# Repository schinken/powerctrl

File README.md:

# DEPRECATED!

For a modern version, look here: https://github.com/b4ckspace/PowerControl

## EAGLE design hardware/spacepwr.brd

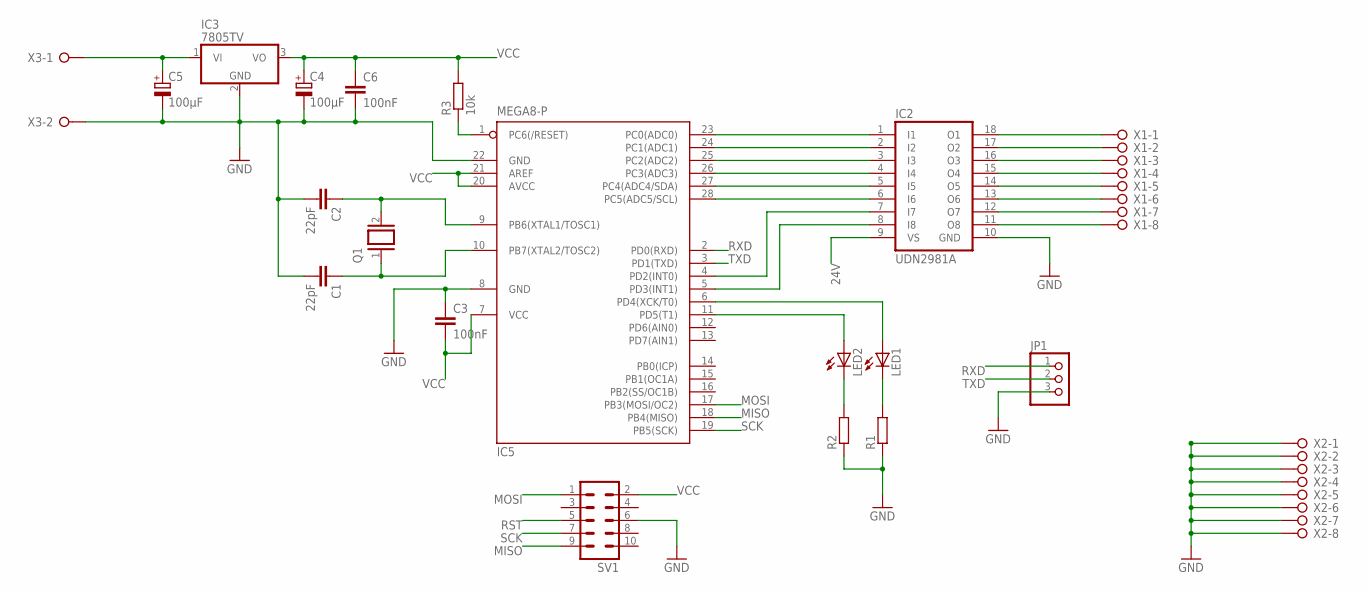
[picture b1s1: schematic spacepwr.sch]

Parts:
C1, C2: 22pF; C025-030X050
C3, C6: 100nF; C025-030X050
C4, C5: 100µF; E5-10,5
IC2: UDN2981A; DIL18
IC3: 7805TV; TO220V
IC5: MEGA8-P; DIL28-3
JP1: PINHD-1X3; 1X03
LED1, LED2: LED5MM
Q1: XTAL/S; QS
R1, R2: R-EU_0207/10; 0207/10
R3: 10k; 0207/10
SV1: ML10
X1, X2: W237-08P; W237-8P
X3: W237-02P; W237-132

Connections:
24V: C5.+, IC2.9 (VS), IC3.1 (VI), X3.1
GND: C1.2, C2.2, C3.1, C4.-, C5.-, C6.2, IC2.10 (GND), IC3.2 (GND), IC5.8 (GND), IC5.22 (GND), JP1.3, R1.1, R2.1, SV1.6, X2.1, X2.2, X2.3, X2.4, X2.5, X2.6, X2.7, X2.8, X3.2
MISO: IC5.18 (PB4(MISO)), SV1.9
MOSI: IC5.17 (PB3(MOSI/OC2)), SV1.1
unnamed: IC2.1 (I1), IC5.23 (PC0(ADC0))
unnamed: IC2.2 (I2), IC5.24 (PC1(ADC1))
unnamed: IC2.3 (I3), IC5.25 (PC2(ADC2))
unnamed: IC2.4 (I4), IC5.26 (PC3(ADC3))
unnamed: IC2.5 (I5), IC5.27 (PC4(ADC4/SDA))
unnamed: IC2.6 (I6), IC5.28 (PC5(ADC5/SCL))
unnamed: IC2.7 (I7), IC5.4 (PD2(INT0))
unnamed: IC2.8 (I8), IC5.5 (PD3(INT1))
unnamed: LED1.K (C), R1.2
unnamed: IC5.6 (PD4(XCK/T0)), LED1.A
unnamed: IC2.18 (O1), X1.1
unnamed: IC5.11 (PD5(T1)), LED2.A
unnamed: LED2.K (C), R2.2
unnamed: IC2.17 (O2), X1.2
unnamed: IC2.16 (O3), X1.3
unnamed: IC2.15 (O4), X1.4
unnamed: C1.1, IC5.10 (PB7(XTAL2/TOSC2)), Q1.1
unnamed: C2.1, IC5.9 (PB6(XTAL1/TOSC1)), Q1.2
unnamed: IC2.14 (O5), X1.5
unnamed: IC2.13 (O6), X1.6
unnamed: IC2.12 (O7), X1.7
unnamed: IC2.11 (O8), X1.8
RST: IC5.1 (PC6(/RESET)), R3.1, SV1.5
RXD: IC5.2 (PD0(RXD)), JP1.1
SCK: IC5.19 (PB5(SCK)), SV1.7
TXD: IC5.3 (PD1(TXD)), JP1.2
VCC: C3.2, C4.+, C6.1, IC3.3 (VO), IC5.7 (VCC), IC5.20 (AVCC), IC5.21 (AREF), R3.2, SV1.2

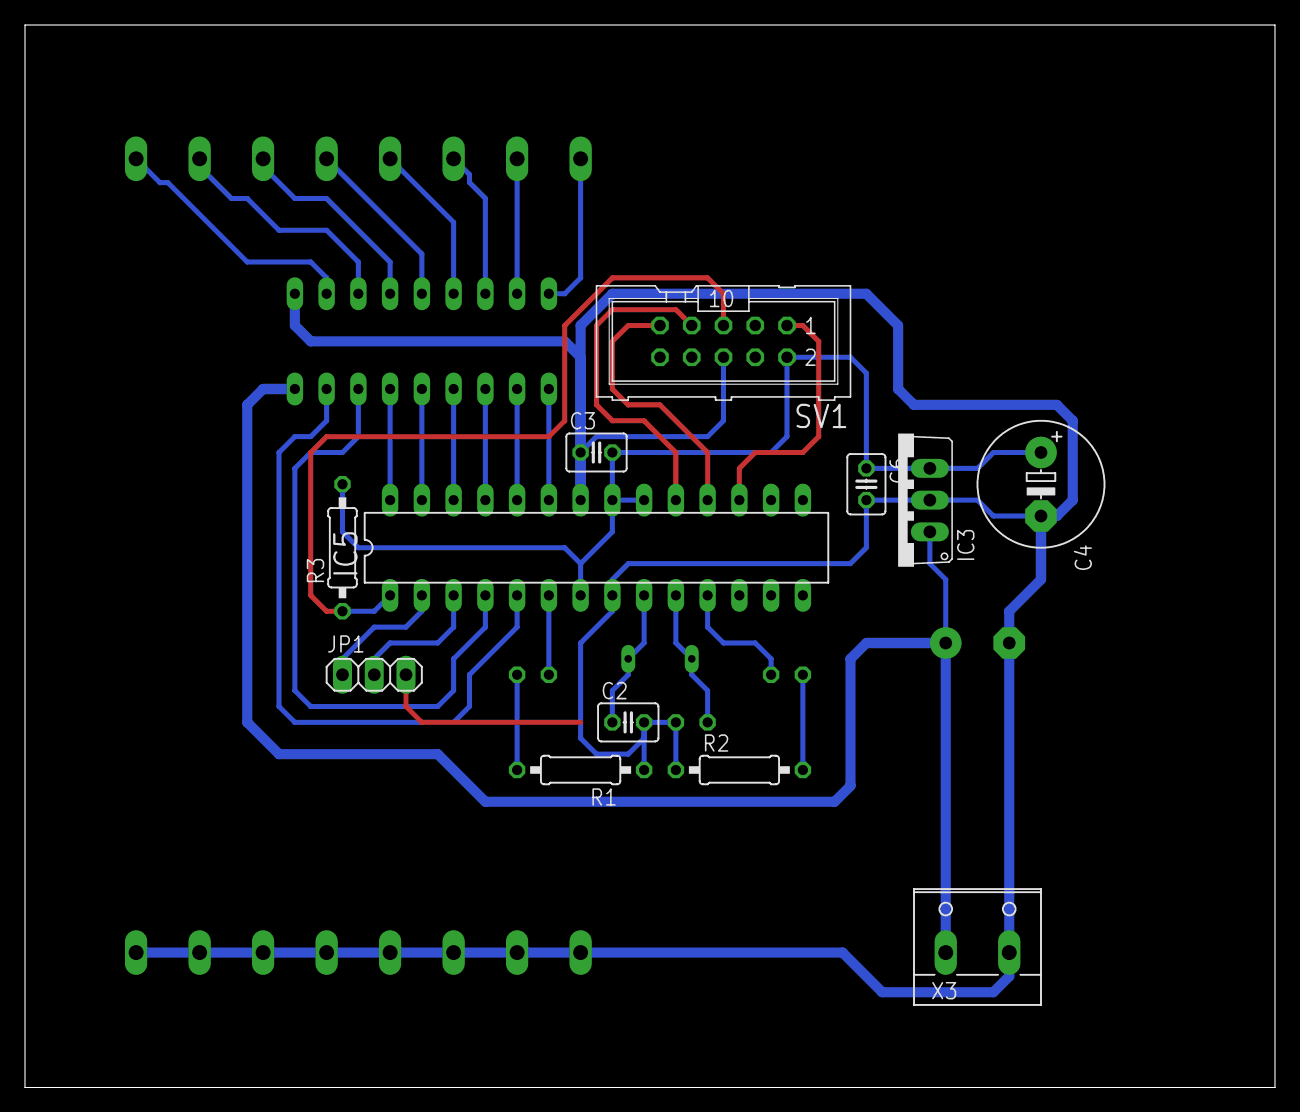
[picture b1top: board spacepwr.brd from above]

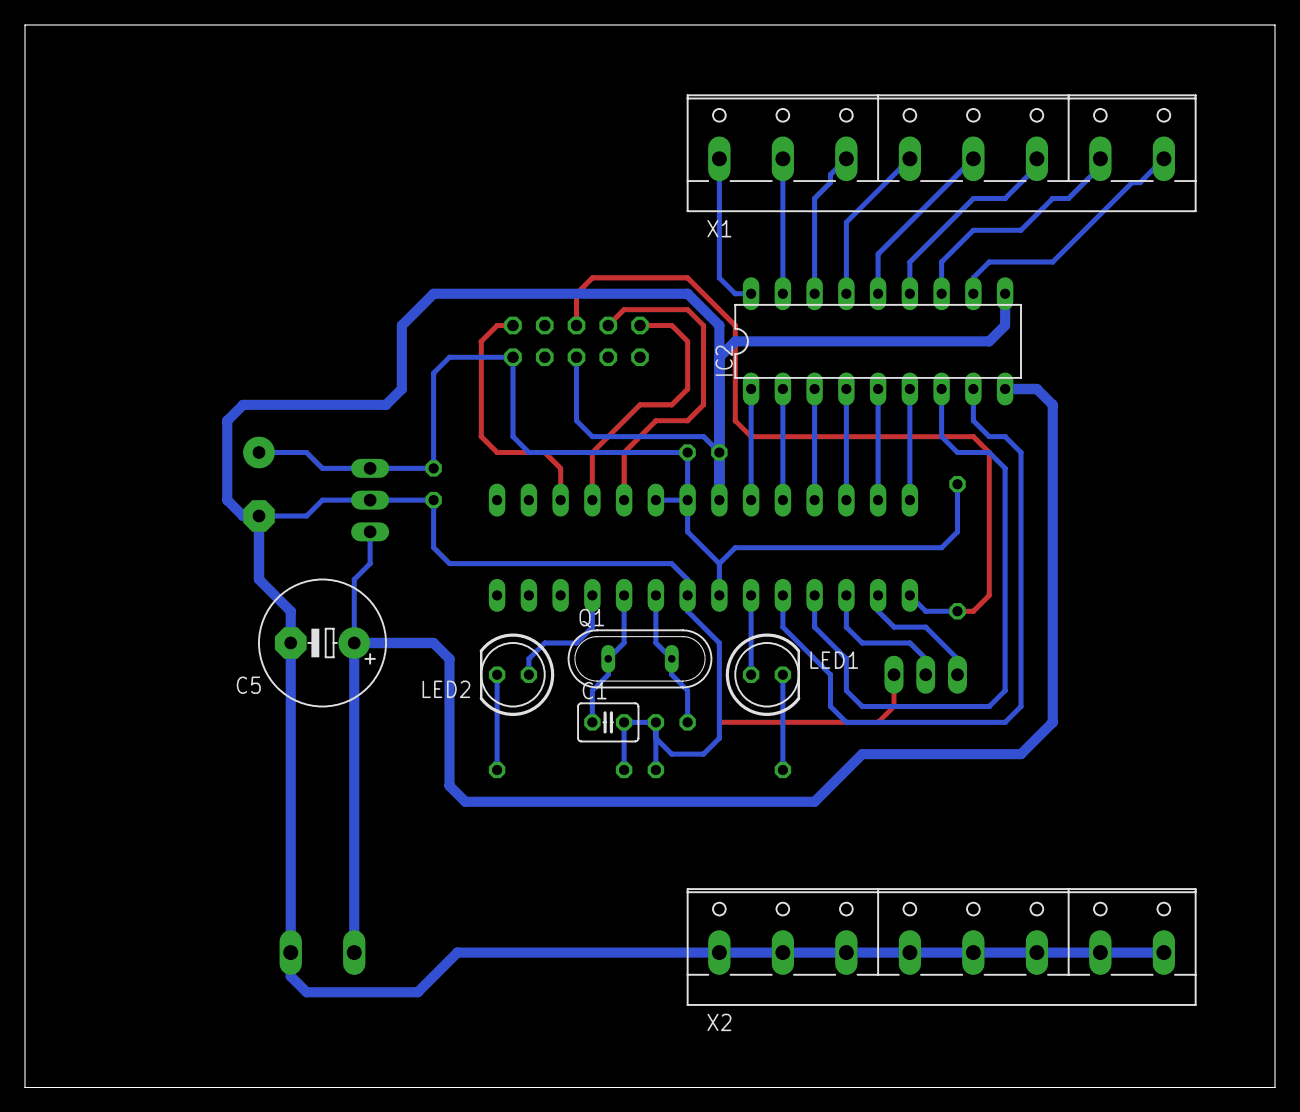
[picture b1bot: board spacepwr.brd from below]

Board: 2 copper layers, 100.0 x 85.0 mm, 20 parts (8 on the bottom side), 31 nets.

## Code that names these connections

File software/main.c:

#include "main.h"
#include <avr/io.h>
#include <avr/interrupt.h>
#include <util/delay.h>
#include <avr/pgmspace.h>

#define USART_BAUD 9600

#define SEND_NEWLINE uart_putc(0x0A); uart_putc(0x0D);


static inline int uart_putc (const uint8_t c)
{
    while (!(UCSRA & (1 << UDRE)));
    UDR = c;
    return 1;
}
void uart_puts (const char *s){
    do{
        uart_putc (*s);
    }while (*s++);
}


///////////////////////////////////////////
// PORTMAPPING
//
// PIN 0 - pd3
// PIN 1 - pd2
// PIN 2 - pc5
// PIN 3 - pc4
// PIN 4 - pc3
// PIN 5 - pc2
// PIN 6 - pc1
// PIN 7 - pc0

const uint8_t portmap[8] = {PIN3,PIN2,PIN5,PIN4,PIN3,PIN2,PIN1,PIN0};

void switch_port(uint8_t port, uint8_t value) {
    
    volatile uint8_t *pport = 0;

    // PIN 0 and 1 is on a different port
    if(port == 0 || port == 1) {
        pport = &PORTD;    
    } else {
        pport = &PORTC;    
    }

    uint8_t tmp = portmap[port];
    
    if(value == 0) {
        *pport &= ~(1<<tmp);    
    } else {
        *pport |= (1<<tmp);    
    }
}

#define STAGE_FLOOR     0
#define STAGE_SET       1
#define STAGE_SINGLE    2
#define STAGE_ALL       3
#define STAGE_PORT      4
#define STAGE_DOT       5
#define STAGE_VALUE     6
#define STAGE_FINAL     7

volatile uint8_t  stage = STAGE_FLOOR
                 ,port = 0
                 ,val = 0
                 ,tmp = 0
                 ,led_off = 0;

        uint16_t led_cnt = 0;

ISR(USART_RXC_vect){

    uint8_t data = UDR;

    // Echo input
    uart_putc(data);

    // Example commands
    // sp0.1 (switch on single port 0)
    // sp0.0 (switch off single port 0)
    // sa0   (switch off everything)
    // sa1   (switch on everything)

    switch(stage) {
        case STAGE_FLOOR:

            port = 0;

            if(data == 's') {
                stage = STAGE_SET;
            }

            break;

        case STAGE_SET:

            if(data == 'p') {
                stage = STAGE_SINGLE;
            } else if (data == 'a') {
                stage = STAGE_ALL;
            } else {
                stage = STAGE_FLOOR;
            }

            break;

        case STAGE_SINGLE:

            tmp = data-48;
            if(tmp >= 0 || tmp <= 7) {
                port = tmp;
                stage = STAGE_DOT;
            } else {
                stage = STAGE_FLOOR;
            }

            break;

        case STAGE_ALL:

            port = 0xFF;
            tmp = data-48;
            if(tmp == 0 || tmp == 1) {
                val = tmp;
                stage = STAGE_FINAL;
            } else {
                stage = STAGE_FLOOR;
            }

            break;

        case STAGE_DOT:

            if(data == '.') {
                stage = STAGE_VALUE;
            } else {
                stage = STAGE_FLOOR;
            }

            break;

        case STAGE_VALUE:

            tmp = data-48;

            if( tmp == 0 || tmp == 1 ) {
                val = tmp;
                stage = STAGE_FINAL;
            } else {
                stage = STAGE_FLOOR;    
            }

            break;

        case STAGE_FINAL:

            if( data == '\r' ) {

                PORTD |= (1<<PIN4);
                led_off = 1;
                led_cnt = 200;

                if( port == 0xFF ) {
                    for( tmp = 0; tmp < 8;tmp++ ) {
                        switch_port( tmp, val );
                    }
                } else {
                    switch_port( port, val );
                }
                
                SEND_NEWLINE;
                uart_puts("OK");
                SEND_NEWLINE;

                stage = STAGE_FLOOR;
            } else {
                stage = STAGE_FLOOR;
            }

            break;
    }

}

int main (void) {            

    UCSRC = (1<<USBS) | (1<<UCSZ1) | (1<<UCSZ0); // 2 stop bits, 8 data bits
    UCSRB = (1<<RXEN) | (1<<RXCIE) | (1<<TXEN);  // enable transmit, receive and interrupts

    uint16_t ubrr = (uint16_t) ((uint32_t) F_CPU/(16UL*USART_BAUD) - 1);

    UBRRH = (uint8_t) (ubrr>>8);
    UBRRL = (uint8_t) (ubrr);

    DDRD |= (1<<PIN5) | (1<<PIN3) | (1<<PIN2);
    DDRC |= (1<<PIN5) | (1<<PIN4) | (1<<PIN3) | (1<<PIN2) | (1<<PIN1) | (1<<PIN0);

    DDRB |= (1<<PIN1);

    DDRD  |= (1<<PIN4);

    sei();

    while(1) {
        if(led_off==1) {
            if(led_cnt == 0) {
                led_off = 0;
                PORTD &= ~(1<<PIN4);
            } else {
                led_cnt--;    
            }
        }
    }

    return 0;                 

}

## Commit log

2012-11-12 added needed parts
2012-11-12 first schematic commit
2012-11-12 added gitignore
2012-11-23 ingoring backup files
2012-11-23 added screw terminals
2012-11-23 routed board
2012-11-23 removed debug output
2012-11-23 Added ACK
2012-11-23 changed max port to 7
2013-02-10 code cleanup
2014-07-03 Add api
2014-07-03 remove swp file
2014-07-03 Remove pyc
2014-07-03 Fix function call
2014-07-03 Send newline
2014-07-03 Fix serial comm
2014-07-03 Fix ack check
2014-07-03 Send \r instead of \n
2014-07-20 Add arduino software
2014-07-20 Add readme
2014-07-20 Add gitignore
2014-07-20 Add sleep
